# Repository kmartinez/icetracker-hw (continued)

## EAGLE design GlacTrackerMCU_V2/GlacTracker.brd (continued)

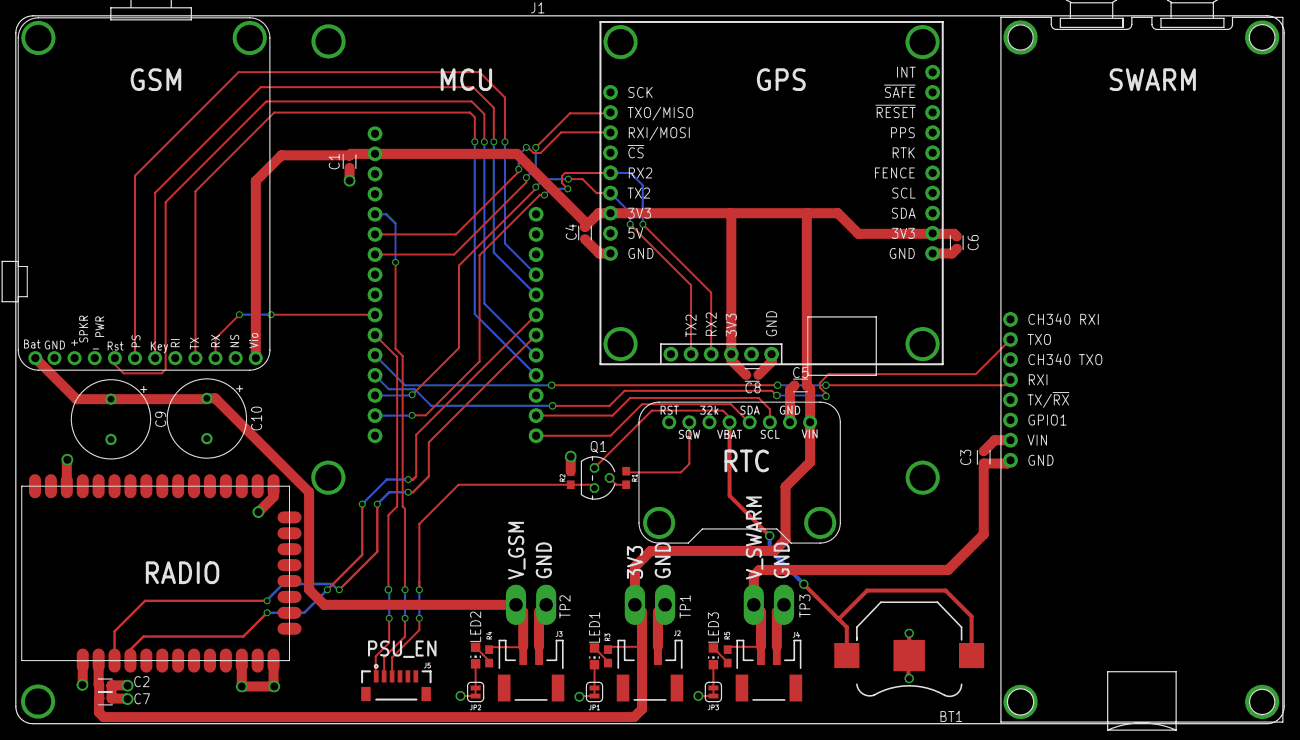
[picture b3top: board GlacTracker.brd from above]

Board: 2 copper layers, 160.0 x 89.3 mm, 36 parts (0 on the bottom side), 31 nets.

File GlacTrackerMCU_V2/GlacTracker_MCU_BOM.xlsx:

Designator | Quantity | Value | Footprint | Description
BT1 |  | 3000TR | BAT_3000TR | Ultra Low Profile SMT Coin Cell Battery Contact Retainer for 12 mm Cell
C1, C2, C3, C4, C6, C8 |  | 100n | 0603 | Capacitor - Generic
C5 |  | 1uF | 0603 | Capacitor - Generic
C7 |  | 100pf | 0603 | Capacitor - Generic
C9, C10 |  | 470uF | TH | Capacitor Polarised - Generic
J1 |  | SPARKFUN-SAMD51-THINGPLUS | TH
J2, J3, J4 |  |  | JST-2-SMD | JST 2MM MALE RA CONNECTOR
J5 |  | JST_6_PIN_VERTICAL | JST-6-SMD-VERT-1.0MM | JST 6 pin vertical connector
LED1, LED2, LED3 |  |  | CHIP-LED0805 | LED
Q1 |  | 2N3906 | TO92 | PNP Transistor
R1, R2 |  | 100k | 0603 | Generic Resistor Package
R3, R4, R5 |  | 1k | 0603 | Generic Resistor Package
U1 |  | DS3231-BREAKOUT | TH
U2 |  | FONA-800-BREAKOUT | TH
U4 |  | SPARKFUN-SWARM-M138 | TH
U5 |  | SPARKFUN-GPS-ZED-F9P | TH
XB1 |  | XBEE-SX868 | TH | XBee(TM)/XBee-PRO(TM) ZB SMT RF Modules.

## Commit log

2023-02-03 edited out future/old options
2023-04-12 add Eagle git ignore, add initial progress on the combined board
2023-04-13 progress
2023-04-17 Complete board for checking and naming
2023-04-17 added a break line
2023-04-18 pre-tweak commt
2023-04-18 DRCand ERC run. Some tweaks to make to the Swarm/GSMoverlap
2023-04-18 missed and airwire
2023-04-19 track tweak
2023-04-19 Add a logo
2023-04-19 Added accelerometer
2023-04-20 Change Key to be grounded and add an Admin pinheader for a button
2023-04-21 Fix the overlapping holes DRC
2023-04-21 Add BatVolts divider values
2023-04-21 update the silkscreen
2023-04-25 Rename to IT3
2023-04-25 Added Eagle 9 version
2023-04-25 Firx DRC issues in Eagle 9
2023-04-25 Final silkscreen tweaks and generation of production files
2023-04-26 Tweaks to PCB, BOM and CPL for production. Should be ready to run
2023-05-02 Update 4V PSUvalues
2023-05-04 updated readme brief on IT3
2023-05-26 Fixes for accelerometer CS pullup
2023-06-23 Properly fix the accelerometer issue and move the GPS power FET slightly
